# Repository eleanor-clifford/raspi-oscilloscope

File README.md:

| :exclamation:  | This is a mirror of [https://git.sr.ht/~ecc/raspi-oscilloscope](https://git.sr.ht/~ecc/raspi-oscilloscope). Please refrain from using GitHub's issue and PR system.  |
|----------------|:-------------------------------------------------------------------------------------------------------------------------------------------------------|

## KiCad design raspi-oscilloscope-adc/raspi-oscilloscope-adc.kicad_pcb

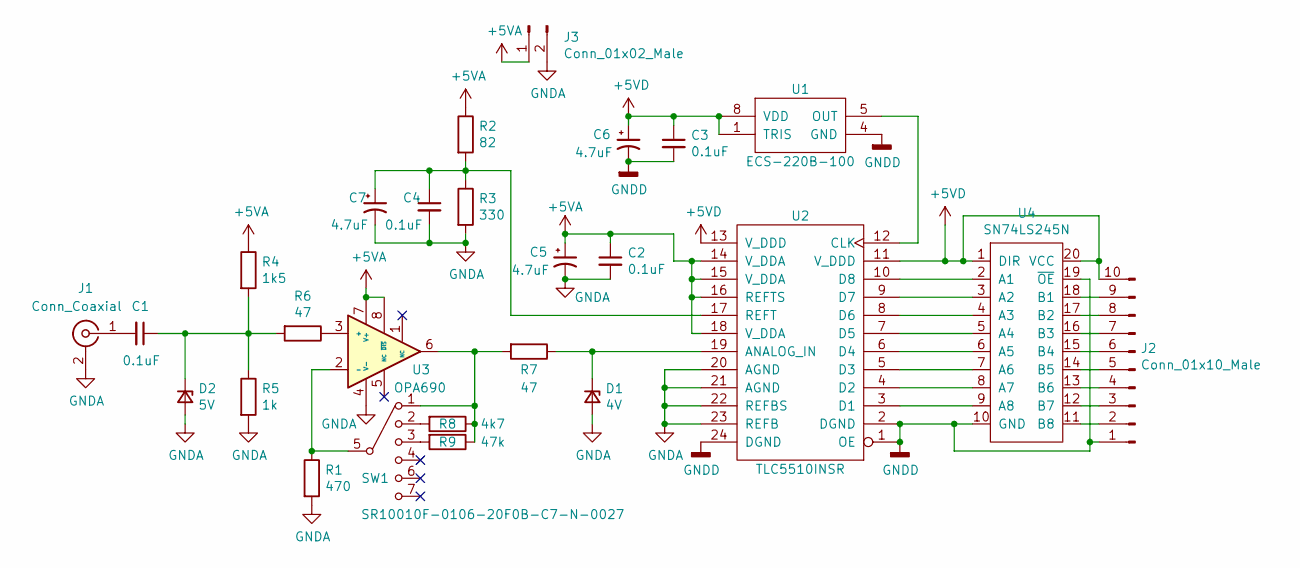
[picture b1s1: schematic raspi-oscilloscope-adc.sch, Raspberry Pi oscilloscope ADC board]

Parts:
C1, C2, C3, C4: 0.1uF; C_Disc_D7.5mm_W5.0mm_P5.00mm
C5, C6, C7: 4.7uF; CP_Radial_D5.0mm_P2.50mm
D1: 4V; D_A-405_P7.62mm_Horizontal
D2: 5V; D_A-405_P7.62mm_Horizontal
J1: Conn_Coaxial; 1-1337543-0
J2: Conn_01x10_Male; PinHeader_1x10_P2.54mm_Vertical
J3: Conn_01x02_Male; PinHeader_1x02_P2.54mm_Vertical
R1: 470; R_Axial_DIN0207_L6.3mm_D2.5mm_P7.62mm_Horizontal
R2: 82; R_Axial_DIN0207_L6.3mm_D2.5mm_P7.62mm_Horizontal
R3: 330; R_Axial_DIN0207_L6.3mm_D2.5mm_P7.62mm_Horizontal
R4: 1k5; R_Axial_DIN0207_L6.3mm_D2.5mm_P7.62mm_Horizontal
R5: 1k; R_Axial_DIN0207_L6.3mm_D2.5mm_P7.62mm_Horizontal
R6, R7: 47; R_Axial_DIN0207_L6.3mm_D2.5mm_P7.62mm_Horizontal
R8: 4k7; R_Axial_DIN0207_L6.3mm_D2.5mm_P7.62mm_Horizontal
R9: 47k; R_Axial_DIN0207_L6.3mm_D2.5mm_P7.62mm_Horizontal
SW1: SR10010F-0106-20F0B-C7-N-0027; SW_SP6T
U1: ECS-220B-100; Oscillator_DIP-8
U2: TLC5510INSR; DIP-24_W15.24mm
U3: OPA690; DIP-8_W7.62mm
U4: SN74LS245N; DIP-20_W7.62mm

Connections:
+5VA: C2.1, C5.1, J3.1, R2.1, R4.1, U2.14 (V_DDA), U2.15 (V_DDA), U2.16 (REFTS), U2.18 (V_DDA), U3.7 (V+), U3.8 (~DIS)
+5VD: C3.1, C6.1, J2.10, U1.1 (TRIS), U1.8 (VDD), U2.11 (V_DDD), U2.13 (V_DDD), U4.1 (DIR), U4.20 (VCC)
GNDA: C2.2, C4.2, C5.2, C7.2, D1.2 (A), D2.2 (A), J1.2 (Ext), J3.2, R1.2, R3.2, R5.2, U2.20 (AGND), U2.21 (AGND), U2.22 (REFBS), U2.23 (REFB), U3.4 (V-)
GNDD: C3.2, C6.2, J2.1, U1.4 (GND), U2.1 (OE), U2.2 (DGND), U2.24 (DGND), U4.10 (GND), U4.19 (~OE)
unnamed: C1.1, D2.1 (K), R4.2, R5.1, R6.2
unnamed: C1.2, J1.1 (In)
unnamed: C4.1, C7.1, R2.2, R3.1, U2.17 (REFT)
unnamed: D1.1 (K), R7.1, U2.19 (ANALOG_IN)
unnamed: J2.2, U4.11 (B8)
unnamed: J2.3, U4.12 (B7)
unnamed: J2.4, U4.13 (B6)
unnamed: J2.5, U4.14 (B5)
unnamed: J2.6, U4.15 (B4)
unnamed: J2.7, U4.16 (B3)
unnamed: J2.8, U4.17 (B2)
unnamed: J2.9, U4.18 (B1)
unnamed: R1.1, SW1.5, U3.2 (-)
unnamed: R6.1, U3.3 (+)
unnamed: R7.2, R8.1, R9.1, SW1.1, U3.6
unnamed: R8.2, SW1.2
unnamed: R9.2, SW1.3
unnamed: U1.5 (OUT), U2.12 (CLK)
unnamed: U2.3 (D1), U4.9 (A8)
unnamed: U2.4 (D2), U4.8 (A7)
unnamed: U2.5 (D3), U4.7 (A6)
unnamed: U2.6 (D4), U4.6 (A5)
unnamed: U2.7 (D5), U4.5 (A4)
unnamed: U2.8 (D6), U4.4 (A3)
unnamed: U2.9 (D7), U4.3 (A2)
unnamed: U2.10 (D8), U4.2 (A1)

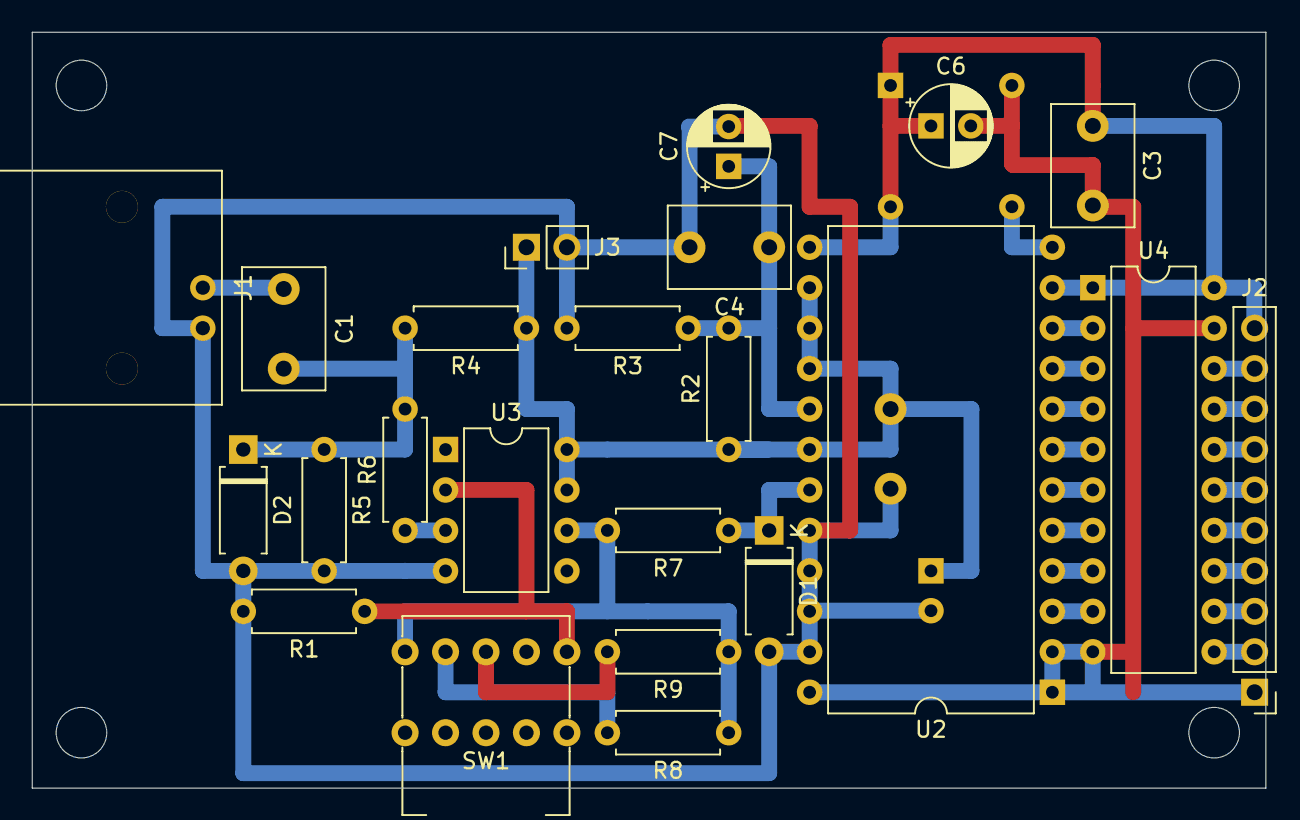
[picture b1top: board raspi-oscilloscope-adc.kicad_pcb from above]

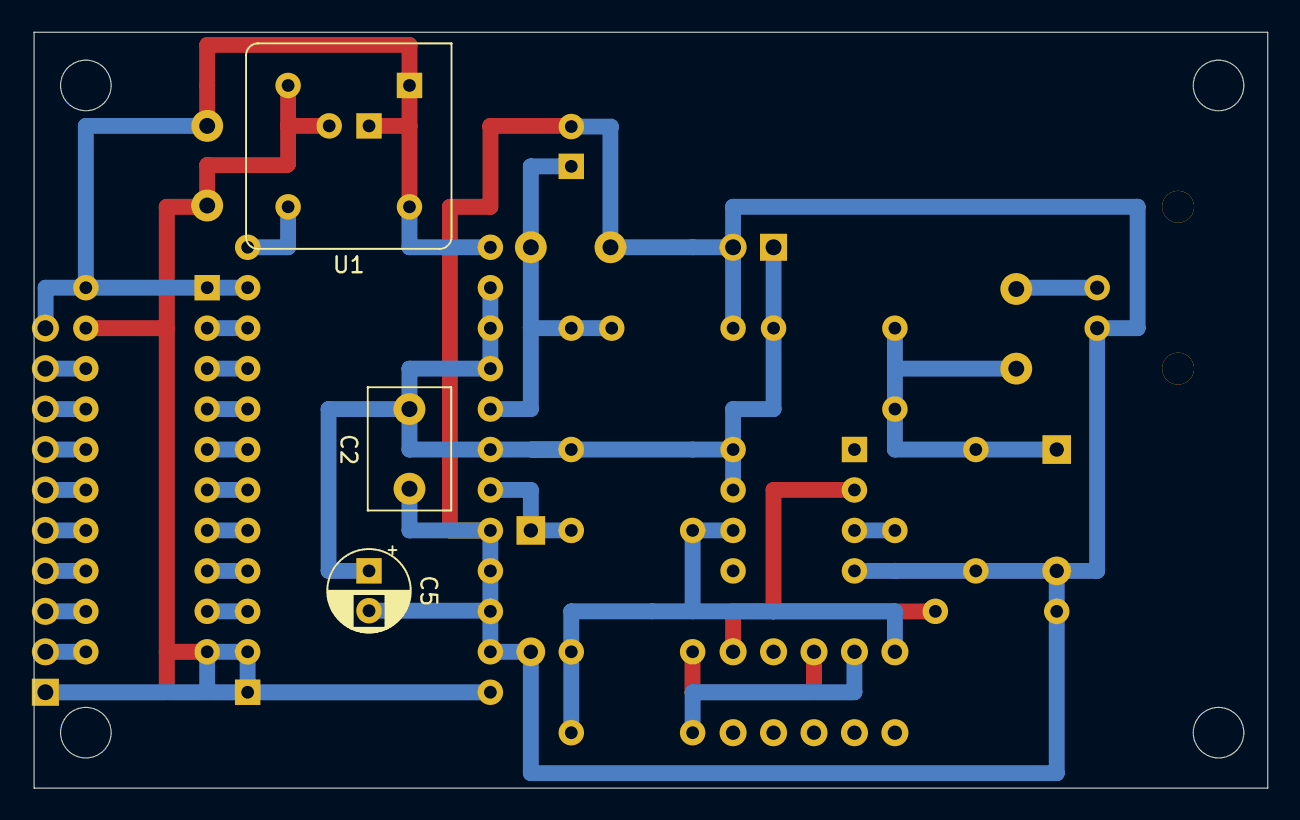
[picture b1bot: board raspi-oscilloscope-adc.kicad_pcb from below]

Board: 2 copper layers, 77.5 x 47.5 mm, 26 parts (3 on the bottom side), 30 nets.

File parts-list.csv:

Name,Part No.,Purpose,Value,Cost
RPi,RPi 1A rev 2,Microprocessor,-,0+
U1,ECS-2200B-100,Clock generator,10 MHz,1.96
U2,TLC5510INSR,ADC,20 MHz 8-bit parallel,5.38
U3,OPA690,Op amp,5V min unipolar,3.01
U4,SN74LS245N,Logic level converter,5V - 3V3,2.99
D1,NZX3V9C,ADC overvolt protection,4V,0.16
D2,NZX5V1B,Op amp reverse/overvolt protection,3V,0.16
C1,-,Input coupling,100nF ceramic,0+
C2,-,Analog bypass,100nF ceramic,0+
C3,-,Digital bypass,100nF ceramic,0+
C4,-,Reference bypass,100nF ceramic,0+
C5,-,Analog bypass,4.7uF electrolytic,0*
C6,-,Digital bypass,4.7uF electrolytic,0*
C7,-,Reference bypass,4.7uF electrolytic,0*
SW1,"SR10010F-0106-20F0B-C7-N-0027 ",Op amp gain switch,SP6T,5.19
R1,-,Op amp gain (low),470,0+
R2,-,ADC reference (high),82,0+
R3,-,ADC reference (low),330,0+
R4,-,Op amp bias (high),1.5k,0+
R5,-,Op amp bias (low),1k,0+
R6,-,Op amp input,47,0+
R7,-,ADC input,47,0+
R8,-,Op amp gain (10x),4k7,0+
R9,-,Op amp gain (100x),47k,0+
A1,-,ADC adapter,SOP-24 to DIP-24,1.67-
A2,-,Op amp adapter,SOP-4 to DIP-4,1.52-
B1,PAD1,Circuit board,DIP 31x19,3.42
J1,1-1337543-0,Probe connector,BNC,1.15
J2,-,Data header,1x8 2.54mm,2.69-
J3,-,Analog power header,1x2 2.54mm,-
-,CQ4LF,Flux,"Liquid, No-Clean",6.30
-,CT2703,Probe,60MHz x1/x10,12.91
,,,Total,45.52
*,scavenged,,VAT,7.93
+,bought earlier,,,
-,includes extra components,,Grand Total,56.44

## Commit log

2025-02-08 Initial testing
2025-02-08 timing
2025-02-08 Test reading+writing to memory
2025-02-08 try 256MiB of data
2025-02-08 output
2025-02-08 a bit more preprocessing
2025-02-08 framebuffer control testing
2025-02-08 more framebuffer stuff
2025-02-08 test max refresh rate
2025-02-08 Maybe faster
2025-02-08 Try grid
2025-02-08 improve
2025-02-08 attempt drawing a character
2025-02-08 bugs
2025-02-08 try drawing more stuff
2025-02-08 Add some lowercase and test
2025-02-08 hopefully compiling on a different raspi is ok
2025-02-08 test without lowercase
2025-02-08 compile
2025-02-08 test
2025-02-08 possibly improve letters and add digit test
2025-02-08 didnt add properly last time lol
2025-02-08 try rising edge triggering
2025-02-08 debugging info
2025-02-08 better debug
2025-02-08 better triggering maybe
2025-02-08 fix byte overflow
2025-02-08 remove debugging
2025-02-08 improve flicker
2025-02-08 Wiring diagram
2025-02-08 Cleanup but probs added lots of bugs
2025-02-08 Improve schematic and add parts list
2025-02-08 Add over/reverse voltage protection diode and smoothing capacitors to schematic
2025-02-08 Finalise parts list; move to kicad; improve schematic; create pcb layout
2025-02-08 Tidy up
2025-02-08 Realign pcb to grid
2025-02-08 Board update
2025-02-08 Add 5V to 3V3 logic converter
2025-02-08 Fix error in board
2025-02-08 Oscilloscope code
2025-02-08 Testing
2025-02-08 Increase background drawing frequency
2025-02-08 Changes for debugging
2025-02-08 stricter triggering
2025-02-08 Move to sourcehut
2025-02-21 [builds.sr.ht] Add mirror warning to README.md
